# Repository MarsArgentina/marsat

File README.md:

# MARSAT

Marsat is an open source project aimed at developing a platform to send student experiments to the upper atmosphere. It's intended to provide it's users the following functionalities:

* GPS tracking

* APRS telemetry

* Flight computer

* Flight termination system

* Parachute

* Battery and energy management

* Bi-directional 900 MHz data link

Experiments are mounted in the upper half of the structure and must comply with 1U cubesat dimmensios. 

The system can provide conectivity and power for up to two 1/2U experiments. 

# Launch and Results 

Balloon was launched on December 16 of 2022, flying to 14KM until the on board computer termiated the flight due to excedinbg the configured geofense. 

Some aquiered data:

Development continues in https://github.com/MarsArgentina/TRXCAN

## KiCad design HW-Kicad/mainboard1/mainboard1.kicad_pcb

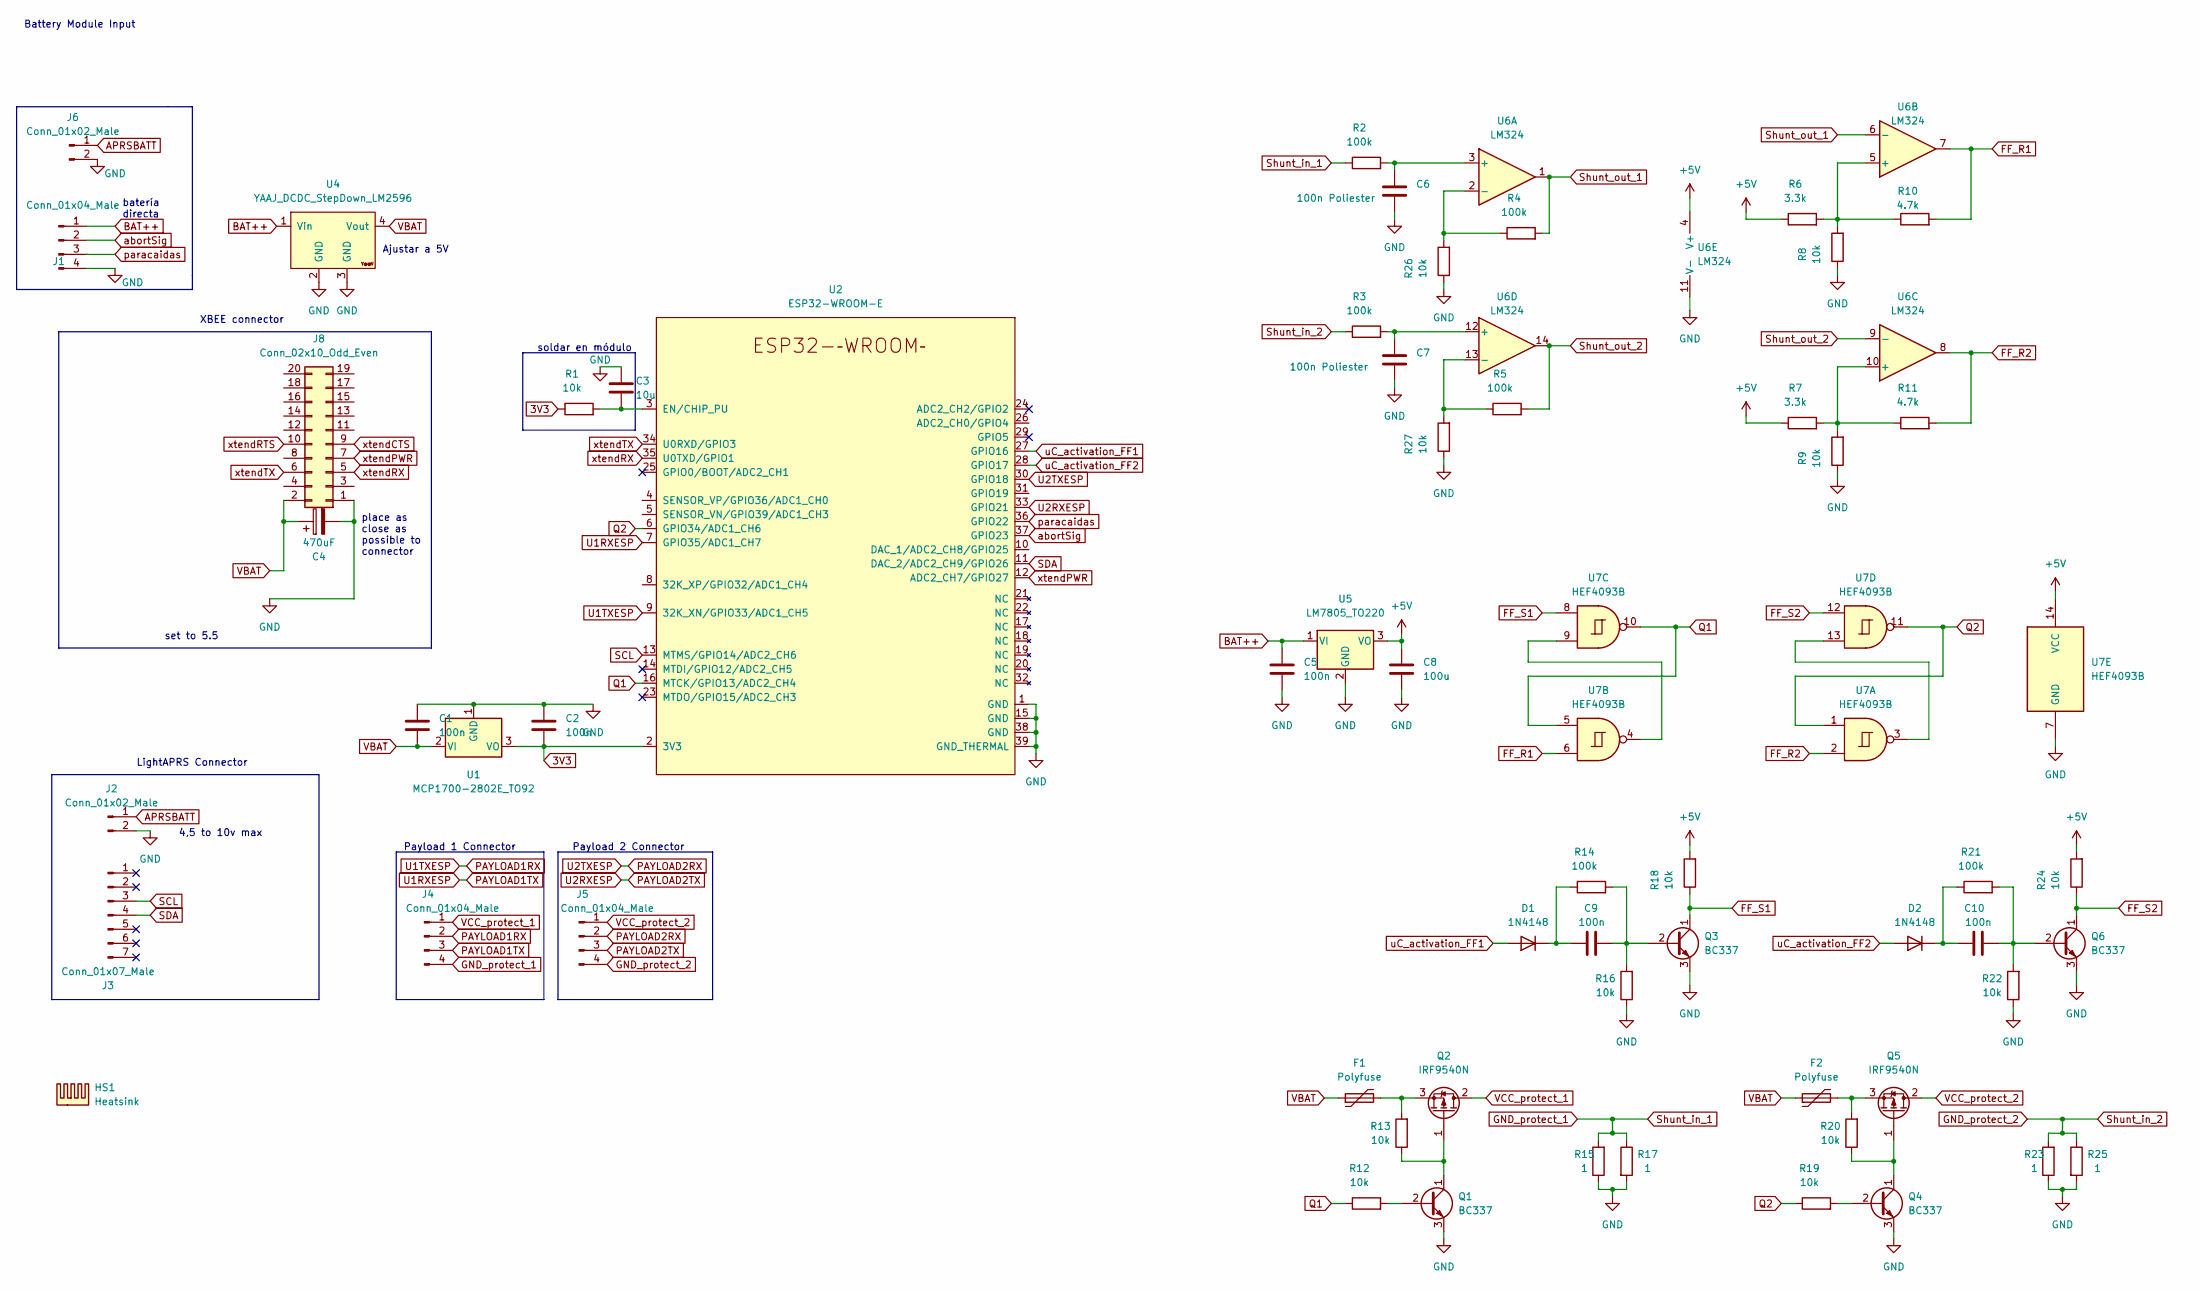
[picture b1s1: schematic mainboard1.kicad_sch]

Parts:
C1, C2, C5, C9, C10: 100n; C_Disc_D3.4mm_W2.1mm_P2.50mm
C3: 10u; CP_Radial_D4.0mm_P2.00mm
C4: 470uF; CP_Radial_D8.0mm_P3.80mm
C6, C7: 100n Poliester; C_Disc_D3.4mm_W2.1mm_P2.50mm
C8: 100u; CP_Radial_D6.3mm_P2.50mm
D1, D2: 1N4148; D_DO-35_SOD27_P7.62mm_Horizontal
F1, F2: Polyfuse; R_Axial_DIN0207_L6.3mm_D2.5mm_P5.08mm_Vertical
HS1: Heatsink; 9xtend
J1, J4, J5: Conn_01x04_Male; Molex_KK-254_AE-6410-04A_1x04_P2.54mm_Vertical
J2: Conn_01x02_Male; PinHeader_1x02_P2.54mm_Horizontal
J3: Conn_01x07_Male; PinHeader_1x07_P2.54mm_Horizontal
J6: Conn_01x02_Male; PinHeader_1x02_P2.54mm_Vertical
J8: Conn_02x10_Odd_Even; PinSocket_2x10_P2.00mm_Vertical
Q1, Q3, Q4, Q6: BC337; TO-92_Inline_Wide
Q2, Q5: IRF9540N; TO-220-3_Vertical
R1, R8, R9, R12, R13, R16, R18, R19, R20, R22, R24, R26, R27: 10k; R_Axial_DIN0207_L6.3mm_D2.5mm_P7.62mm_Horizontal
R2, R3, R4, R5, R14, R21: 100k; R_Axial_DIN0207_L6.3mm_D2.5mm_P7.62mm_Horizontal
R6, R7: 3.3k; R_Axial_DIN0207_L6.3mm_D2.5mm_P7.62mm_Horizontal
R10, R11: 4.7k; R_Axial_DIN0207_L6.3mm_D2.5mm_P7.62mm_Horizontal
R15, R17, R23, R25: 1; R_Axial_DIN0207_L6.3mm_D2.5mm_P7.62mm_Horizontal
U1: MCP1700-2802E_TO92; TO-92_Inline_Wide
U2: ESP32-WROOM-E; esp32_breakout
U4: YAAJ_DCDC_StepDown_LM2596; DC_DC_LM2596_small
U5: LM7805_TO220; TO-220-3_Vertical
U6: LM324; DIP-14_W7.62mm
U7: HEF4093B; DIP-14_W7.62mm

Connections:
3V3: C2.2, R1.1, U1.3 (VO), U2.2 (3V3)
+5V: C8.1, R6.1, R7.1, R18.2, R24.2, U5.3 (VO), U6.4 (V+), U7.14 (VCC)
APRSBATT: J2.1, J6.1
BAT++: C5.1, J1.1, U4.1 (Vin), U5.1 (VI)
FF_R1: R10.2, U6.7, U7.6
FF_R2: R11.2, U6.8, U7.2
FF_S1: Q3.1 (C), R18.1, U7.8
FF_S2: Q6.1 (C), R24.1, U7.12
GND: C1.1, C2.1, C3.1, C4.2, C5.2, C6.2, C7.2, C8.2, J1.4, J2.2, J6.2, J8.1, Q1.3 (E), Q3.3 (E), Q4.3 (E), Q6.3 (E), R8.1, R9.1, R15.1, R16.1, R17.2, R22.1, R23.1, R25.2, R26.1, R27.1, U1.1 (GND), U2.1 (GND), U2.15 (GND), U2.38 (GND), U2.39 (GND_THERMAL), U4.2 (GND), U4.3 (GND), U5.2 (GND), U6.11 (V-), U7.7 (GND)
GND_protect_1: J4.4, R2.1, R15.2, R17.1
GND_protect_2: J5.4, R3.1, R23.2, R25.1
unnamed: C3.2, R1.2, U2.3 (EN/CHIP_PU)
unnamed: C6.1, R2.2, U6.3 (+)
unnamed: C7.1, R3.2, U6.12 (+)
unnamed: C9.1, D1.1 (K), R14.1
unnamed: C9.2, Q3.2 (B), R14.2, R16.2
unnamed: C10.1, D2.1 (K), R21.1
unnamed: C10.2, Q6.2 (B), R21.2, R22.2
unnamed: F1.2, Q2.3 (S), R13.2
unnamed: F2.2, Q5.3 (S), R20.2
unnamed: Q1.1 (C), Q2.1 (G), R13.1
unnamed: Q1.2 (B), R12.2
unnamed: Q4.1 (C), Q5.1 (G), R20.1
unnamed: Q4.2 (B), R19.2
unnamed: R4.1, R26.2, U6.2 (-)
unnamed: R5.1, R27.2, U6.13 (-)
unnamed: R6.2, R8.2, R10.1, U6.5 (+)
unnamed: R7.2, R9.2, R11.1, U6.10 (+)
unnamed: U7.4, U7.9
unnamed: U7.3, U7.13
PAYLOAD1RX: J4.2, U2.9 (32K_XN/GPIO33/ADC1_CH5)
PAYLOAD1TX: J4.3, U2.7 (GPIO35/ADC1_CH7)
PAYLOAD2RX: J5.2, U2.30 (GPIO18)
PAYLOAD2TX: J5.3, U2.33 (GPIO21)
Q1: R12.1, U2.16 (MTCK/GPIO13/ADC2_CH4), U7.5, U7.10
Q2: R19.1, U2.6 (GPIO34/ADC1_CH6), U7.1, U7.11
SCL: J3.3, U2.13 (MTMS/GPIO14/ADC2_CH6)
SDA: J3.4, U2.11 (DAC_2/ADC2_CH9/GPIO26)
Shunt_out_1: R4.2, U6.1, U6.6 (-)
Shunt_out_2: R5.2, U6.9 (-), U6.14
VBAT: C1.2, C4.1, F1.1, F2.1, J8.2, U1.2 (VI), U4.4 (Vout)
VCC_protect_1: J4.1, Q2.2 (D)
VCC_protect_2: J5.1, Q5.2 (D)
abortSig: J1.2, U2.37 (GPIO23)
paracaidas: J1.3, U2.36 (GPIO22)
uC_activation_FF1: D1.2 (A), U2.27 (GPIO16)
uC_activation_FF2: D2.2 (A), U2.28 (GPIO17)
xtendCTS: J8.9
xtendPWR: J8.7, U2.12 (ADC2_CH7/GPIO27)
xtendRTS: J8.10
xtendRX: J8.5, U2.35 (U0TXD/GPIO1)
xtendTX: J8.6, U2.34 (U0RXD/GPIO3)

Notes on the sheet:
Payload 1 Connector
Battery Module Input
Ajustar a 5V
set to 5.5
4,5 to 10v max
XBEE connector
place as close as possible to connector
batería directa
soldar en módulo
Payload 2 Connector
LightAPRS Connector

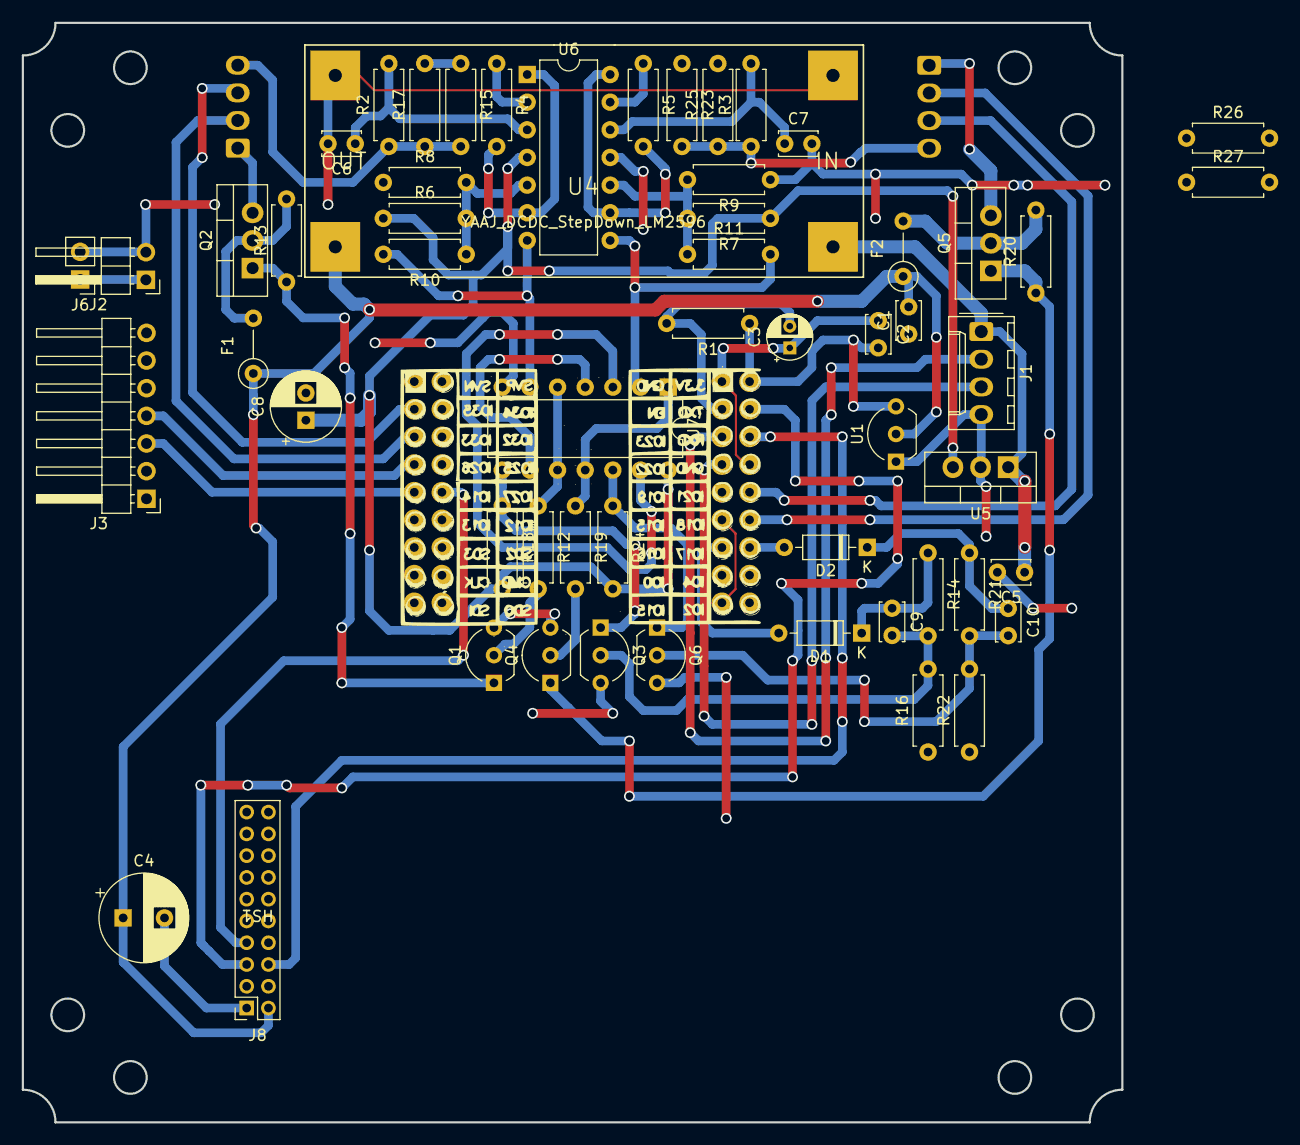
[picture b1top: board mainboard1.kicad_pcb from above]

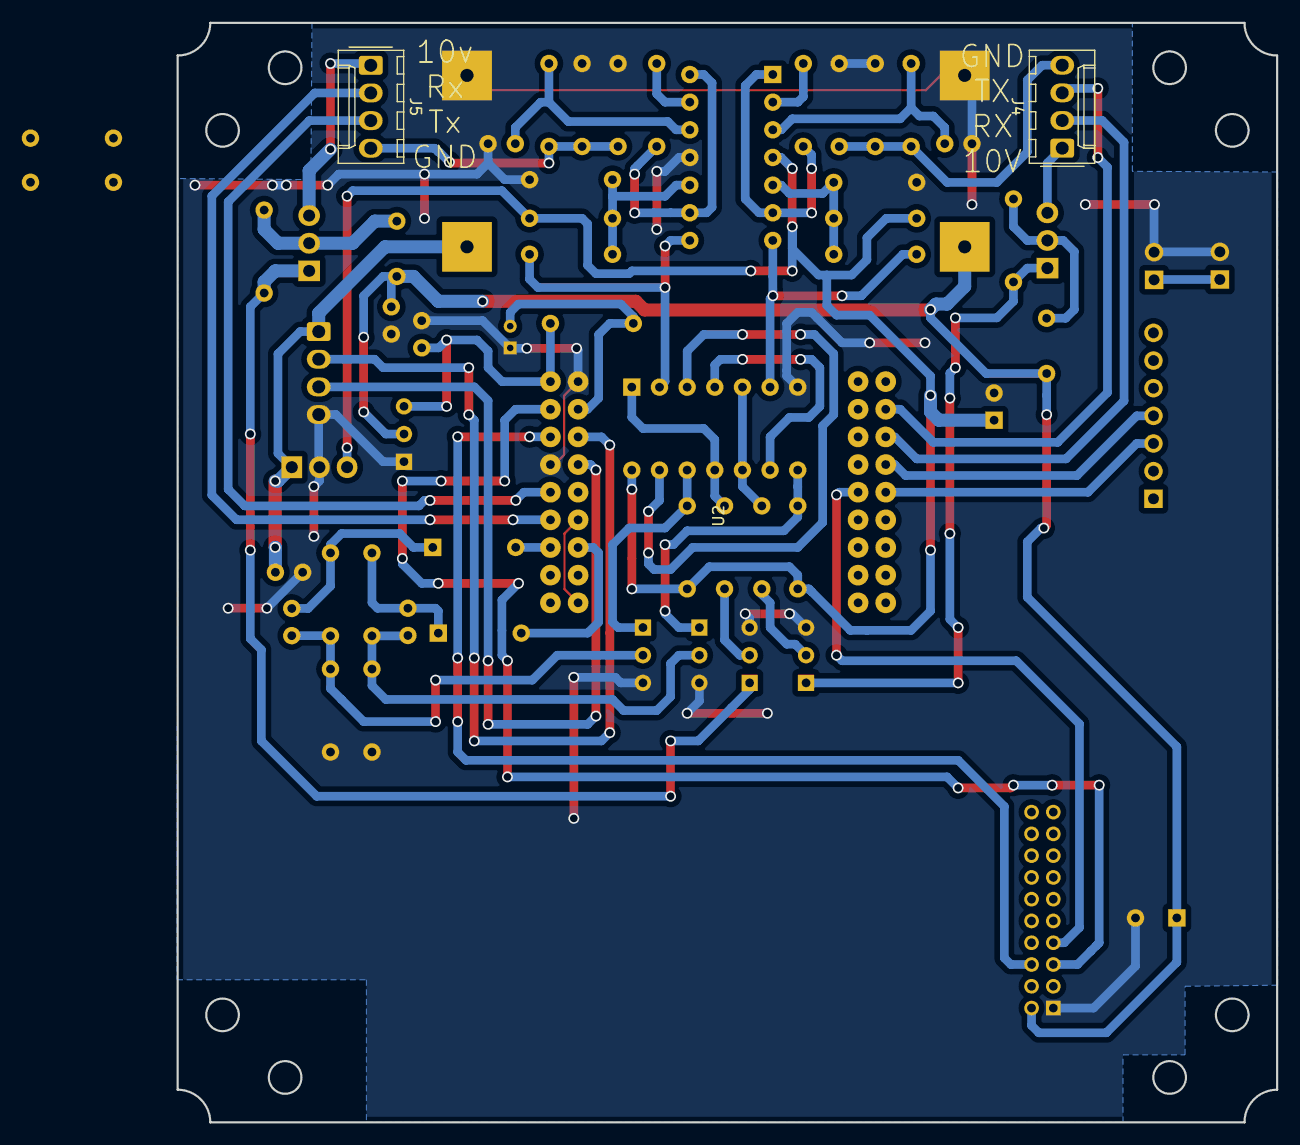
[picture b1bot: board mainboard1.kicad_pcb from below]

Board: 2 copper layers, 101.0 x 101.0 mm, 61 parts (2 on the bottom side), 50 nets.

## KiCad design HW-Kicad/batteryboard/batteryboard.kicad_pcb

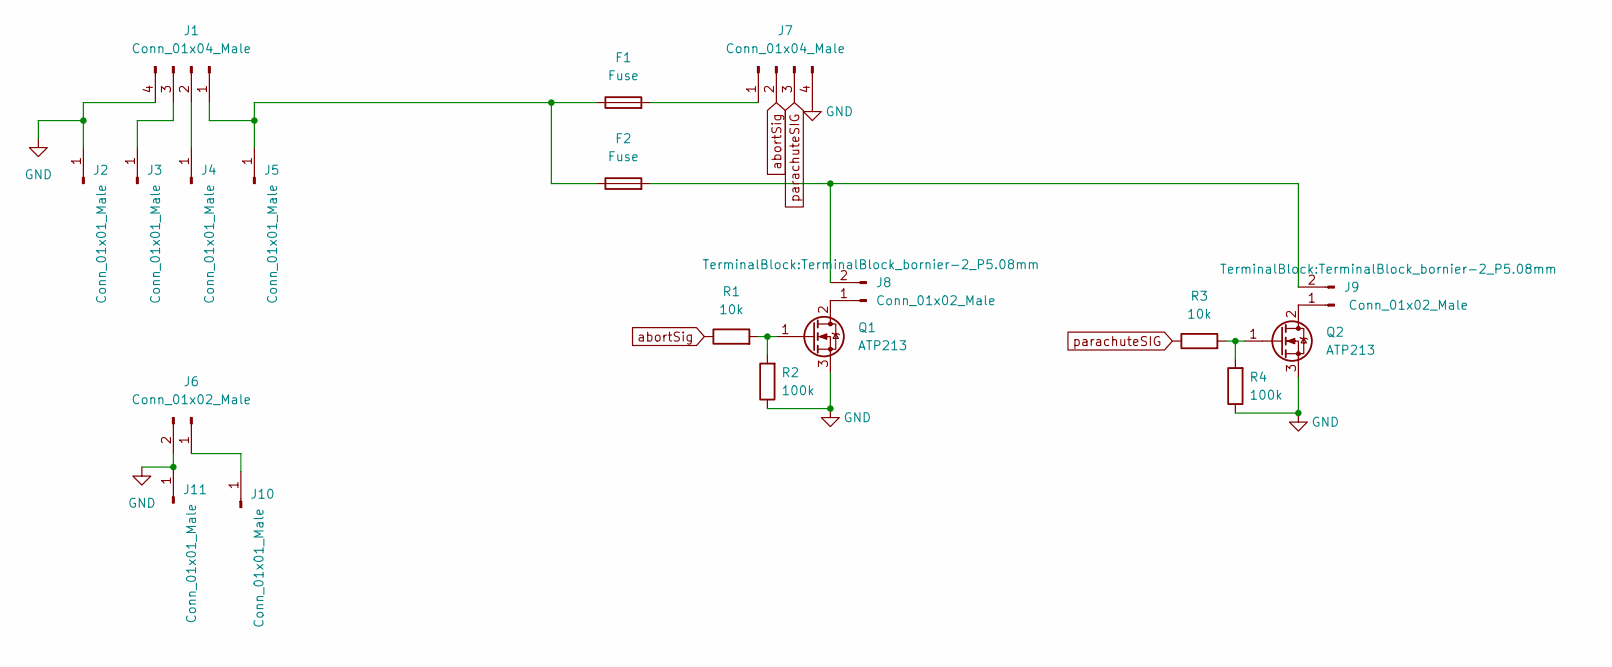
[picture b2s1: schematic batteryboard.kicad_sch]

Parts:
F1, F2: Fuse; Fuseholder_Blade_Mini_Keystone_3568
J1, J7: Conn_01x04_Male; Molex_KK-254_AE-6410-04A_1x04_P2.54mm_Vertical
J2, J3, J4, J5, J10, J11: Conn_01x01_Male; PinHeader_1x01_P2.54mm_Vertical
J6: Conn_01x02_Male; Molex_KK-254_AE-6410-02A_1x02_P2.54mm_Vertical
J8, J9: Conn_01x02_Male; TerminalBlock_bornier-2_P5.08mm
Q1, Q2: ATP213; TO-252-2
R1, R3: 10k; R_Axial_DIN0207_L6.3mm_D2.5mm_P10.16mm_Horizontal
R2, R4: 100k; R_Axial_DIN0207_L6.3mm_D2.5mm_P10.16mm_Horizontal

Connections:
GND: J1.4, J2.1, J6.2, J7.4, J11.1, Q1.3 (S), Q2.3 (S), R2.1, R4.1
unnamed: F1.1, F2.1, J1.1, J5.1
unnamed: F1.2, J7.1
unnamed: F2.2, J8.2, J9.2
unnamed: J1.2, J4.1
unnamed: J1.3, J3.1
unnamed: J8.1, Q1.2 (D)
unnamed: J9.1, Q2.2 (D)
unnamed: J6.1, J10.1
unnamed: Q1.1 (G), R1.2, R2.2
unnamed: Q2.1 (G), R3.2, R4.2
abortSig: J7.2, R1.1
parachuteSIG: J7.3, R3.1

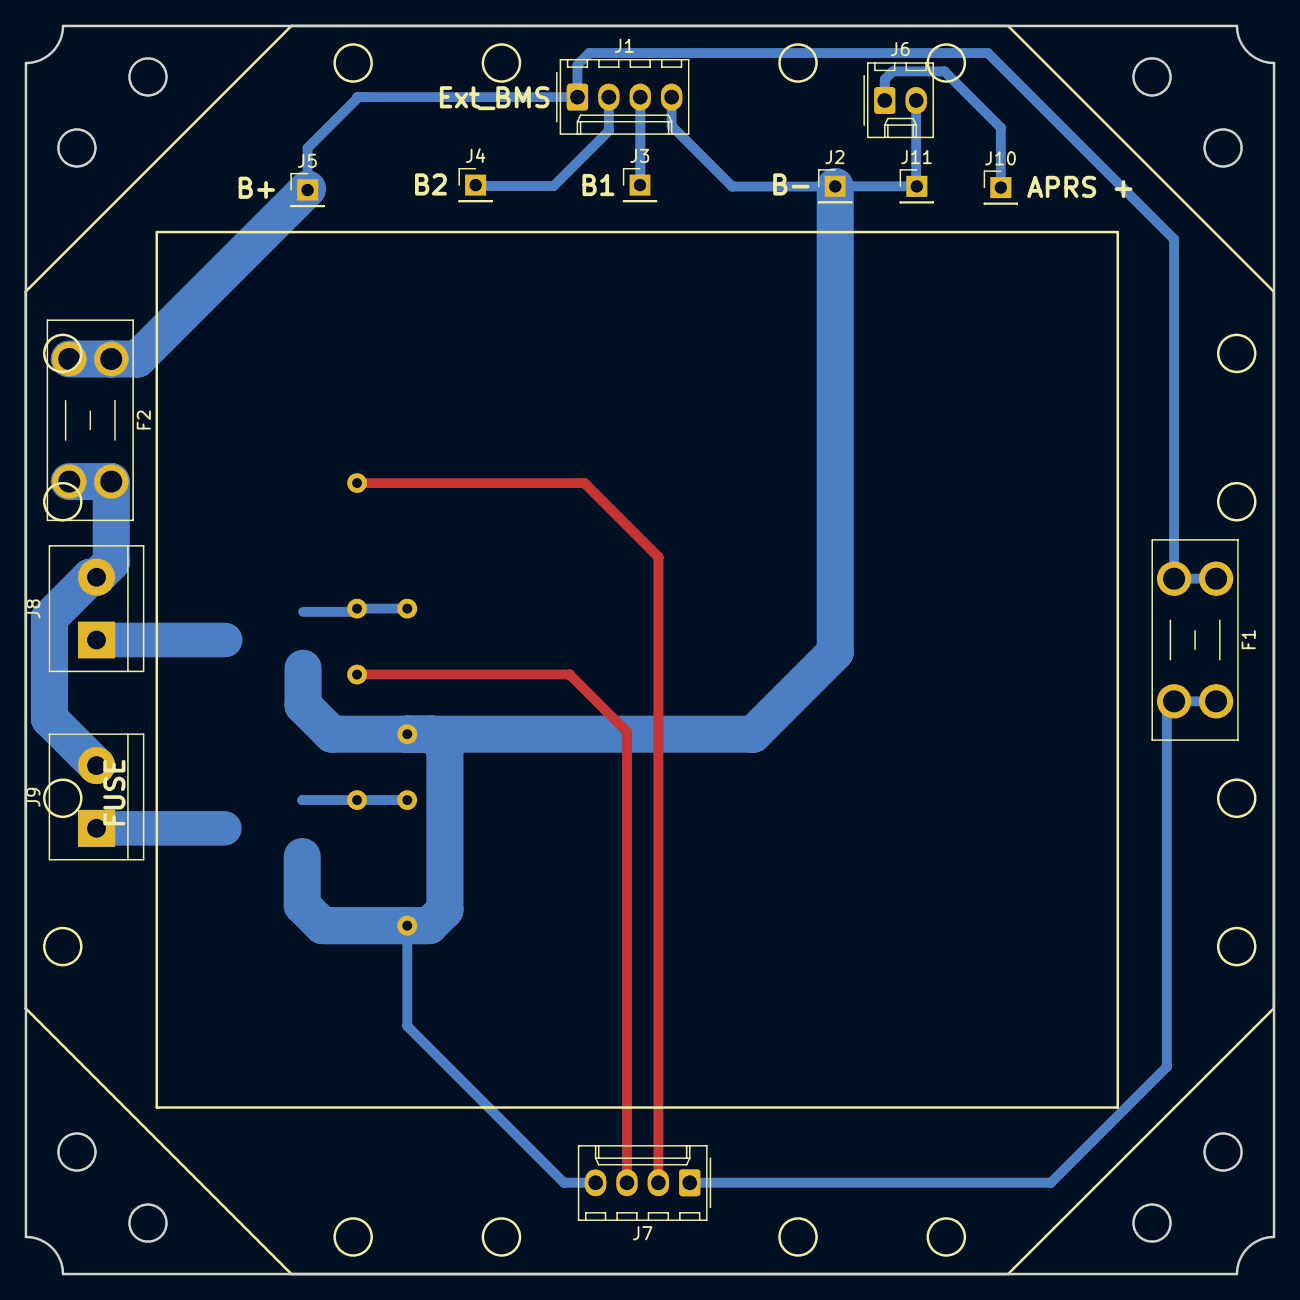
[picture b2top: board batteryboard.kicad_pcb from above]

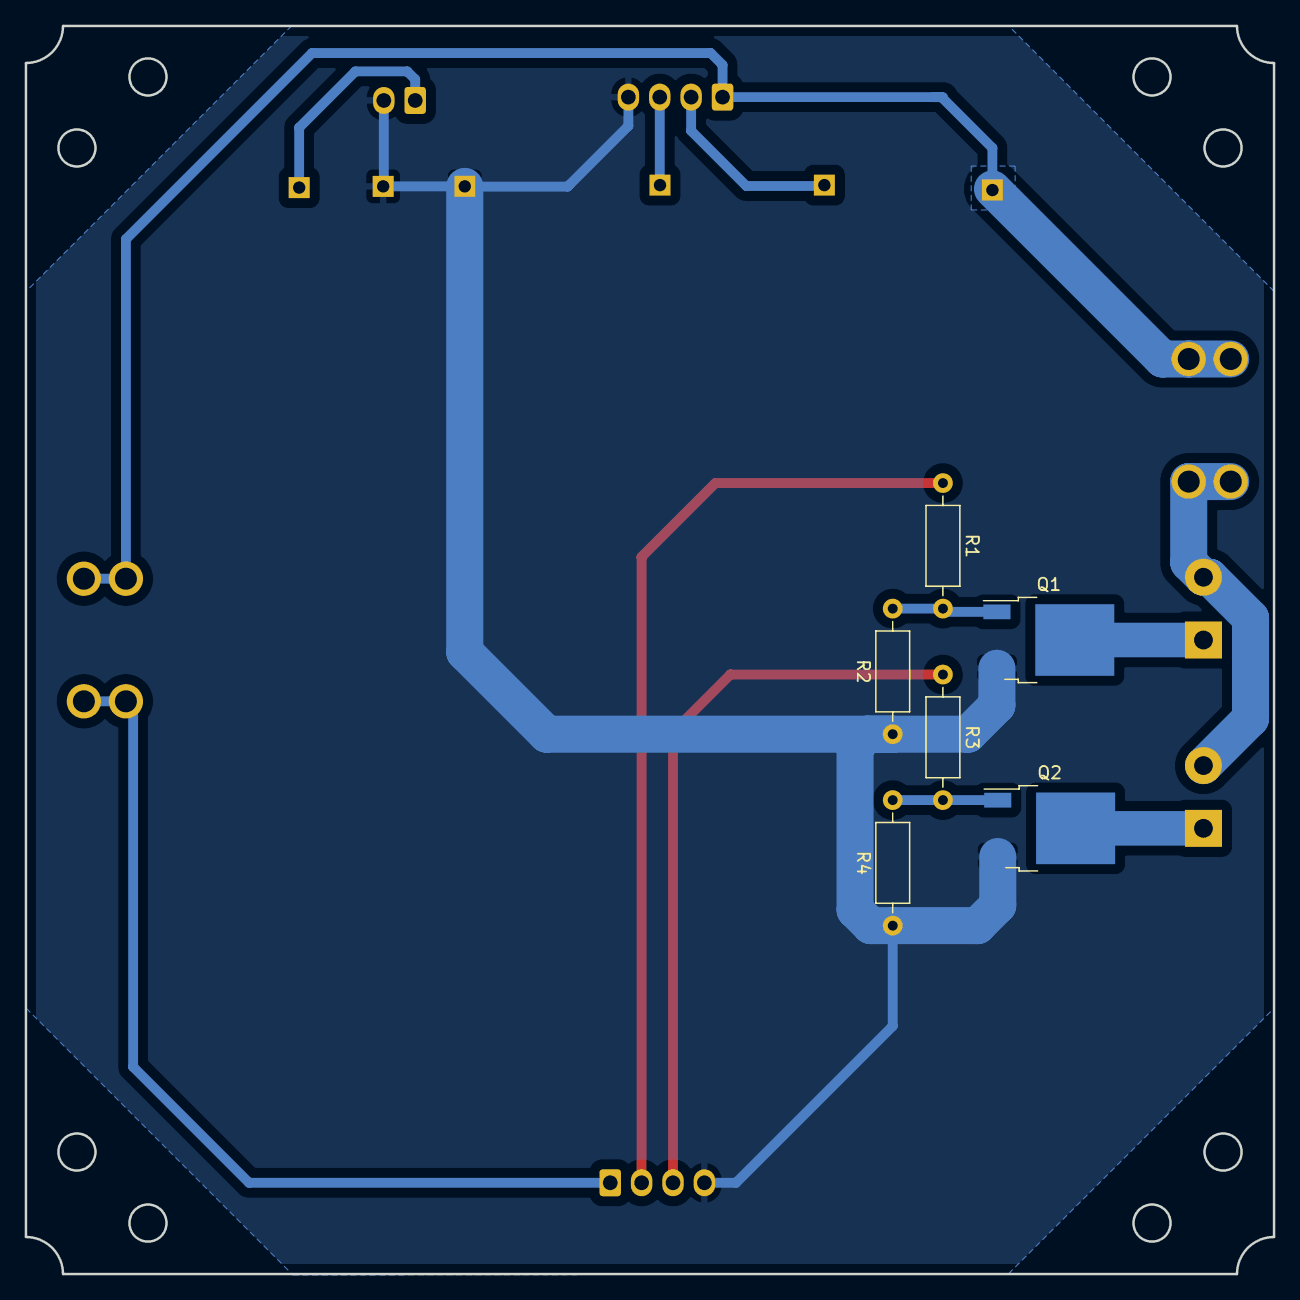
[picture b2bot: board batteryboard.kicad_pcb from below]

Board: 2 copper layers, 101.0 x 101.0 mm, 19 parts (6 on the bottom side), 13 nets.

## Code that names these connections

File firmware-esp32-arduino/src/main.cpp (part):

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#define ALTURA_MAX_VUELOS_COMERCIALES 12000

// 9xtend
#define XTEND_RX 1   // xtendRX
#define XTEND_TX 3   // xtendTX
#define XTEND_PWR 27 // xtendPWR

// payload1
#define PAYLOAD1_RX 35    // U1RXESP
#define PAYLOAD1_TX 33    // U1TXESP
#define PAYLOAD1_CHECK 13 // Q1
#define PAYLOAD1_ON 16    // uC_activation_FF1
#define PAYLOAD1_OFF 25

// payload2
#define PAYLOAD2_RX 21    // U2RXESP
#define PAYLOAD2_TX 18    // U2TXESP
#define PAYLOAD2_CHECK 34 // Q2
#define PAYLOAD2_ON 17    // uC_activation_FF2
#define PAYLOAD2_OFF 19

// lightaprs
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#define LIGHTAPRS_SCL 26 // SCL

// gpio
#define NICROM_PIN 23    // abortSig
#define PARACHUTE_PIN 22 // paracaidas

#define PIN_BATERIA 4

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
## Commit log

2022-08-06 actualizar readme
2022-08-13 inicio de proyecto en kicad
    hice y agregué el símbolo y footprint del módulo lightaprs
2022-08-14 palca de baterias terminada
2022-08-14 comienzo mainboard
2022-08-22 cambio de footprint esp32 y ruteo de algunas pistas
2022-08-28 version final de la batery board
2022-09-07 falta agregar el mosfet que revienta el globo y el dtmf
2022-09-25 agregué un componente de kicad
2022-10-12 agregue circuito de rotura de globo
2022-10-16 inicio firmware
2022-10-17 cosas en mainboard
2022-10-17 agregué fución que obtiene el rssi
2022-10-17 nada
2022-10-17 nuevo firmware en arduino
2022-10-17 empiezo firmware estacion terena
2022-10-18 mainboard terminada
2022-10-18 version final de placa baterías
2022-10-19 actualicé el tamaño de unos pads
2022-10-21 agregue texto para foto
2022-10-22 cambie para tener dos señales de control distintas
2022-10-22 actualicé pines del esp32
2022-10-22 agrego funciones de gps y corrijo defines
2022-10-23 agrego funciones y lógica sin terminar
2022-10-27 agregue pines de baterías para aprs
2022-10-31 importe nueva version de leo
2022-10-31 agegue el conector de energía separado para el aprs
2022-10-31 agrego el firmware custom de lightaprs
2022-11-06 vuelvo a copiar código original
2022-11-06 desactivo wspr, agrego software serial
2022-11-08 quito softwareserial, envía tramas i2c
2022-11-08 agrego sensor temp externo DS18B20
2022-11-15 firmware estacion terrena
2022-11-15 correcciones
    resistencias en operacionales no inversores de medición de corriente y MOSFET invertidos
2022-11-16 continuo firmware esp32
2022-11-17 agrego librería lightaprs
2022-11-18 máquina de estados desarrollada
2022-11-20 agrego comandos UART
2022-11-20 lightaprs envía coord por i2c solo si son válidas
2022-11-22 personalizo mensaje APRS
2022-11-22 corrijo errores, aprs y xtend funcionan
2022-11-23 se corrijió i2c y se agregaron comandos
2022-11-23 corrijo db enviados por uart
2022-11-24 agrego comandos y corrijo configuraciones
2022-11-27 corrijo formato telemetría
    Versión editada sobre GitHub web, sin compilar.
2022-11-29 corrigiendo errores i2c
2022-11-29 paso a software serial
2022-12-01 agrego wdt_resets
2022-12-01 agrego margenes de error a altura gps
2022-12-06 agrego lectura y reporte y de tensión de vaterías
2022-12-12 agrego test esp32
2022-12-13 agrego batería main a msj aprs
2022-12-13 test envía coord ingresadas x terminal
2022-12-14 mejoras en lógica de vuelo
2022-12-15 limpio buffer de entrada lightaprs
2022-12-15 para prueba, no recibe siempre vbatesp
2023-12-15 update readme and images
2023-12-21 add presentation files

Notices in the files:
firmware-esp32-arduino/src/main.cpp:
@copyright Copyright (c) 2022
